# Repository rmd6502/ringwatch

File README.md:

## Welcome to GitHub Pages

You can use the [editor on GitHub](https://github.com/rmd6502/ringwatch/edit/master/README.md) to maintain and preview the content for your website in Markdown files.

Whenever you commit to this repository, GitHub Pages will run [Jekyll](https://jekyllrb.com/) to rebuild the pages in your site, from the content in your Markdown files.

### Markdown

Markdown is a lightweight and easy-to-use syntax for styling your writing. It includes conventions for

```markdown
Syntax highlighted code block

# Header 1
## Header 2
### Header 3

- Bulleted
- List

1. Numbered
2. List

**Bold** and _Italic_ and `Code` text

[Link](url) and 
```

For more details see [GitHub Flavored Markdown](https://guides.github.com/features/mastering-markdown/).

### Jekyll Themes

Your Pages site will use the layout and styles from the Jekyll theme you have selected in your [repository settings](https://github.com/rmd6502/ringwatch/settings). The name of this theme is saved in the Jekyll `_config.yml` configuration file.

### Support or Contact

Having trouble with Pages? Check out our [documentation](https://help.github.com/categories/github-pages-basics/) or [contact support](https://github.com/contact) and we’ll help you sort it out.

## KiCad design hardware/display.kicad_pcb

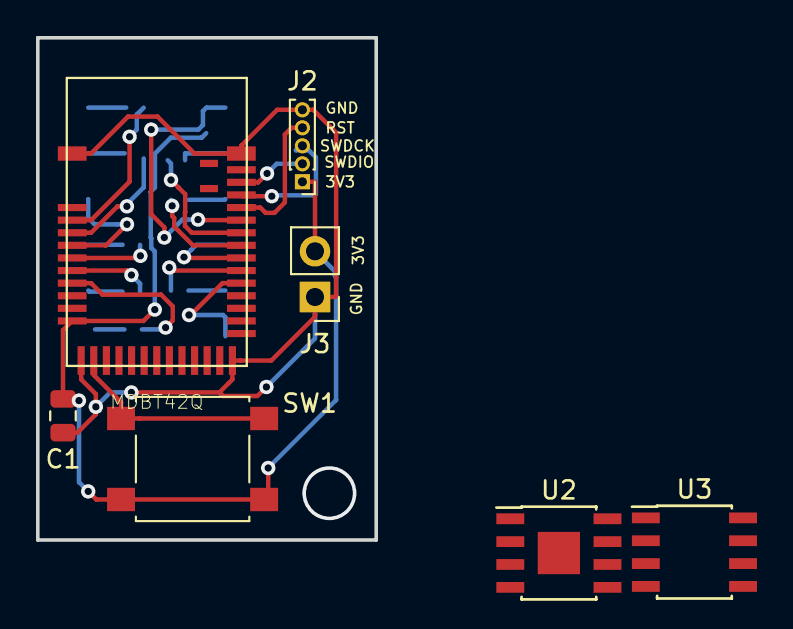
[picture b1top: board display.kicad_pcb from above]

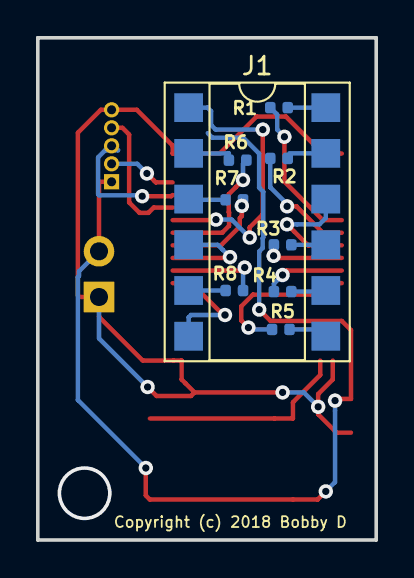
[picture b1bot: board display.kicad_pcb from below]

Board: 2 copper layers, 18.8 x 27.9 mm, 16 parts (9 on the bottom side), 28 nets.

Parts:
C1: .1µ; C_0805_2012Metric
J1: Conn_02x06_Counter_Clockwise; DIP-12_W7.62mm_SMDSocket_SmallPads
J2: Conn_01x05_Female; PinHeader_1x05_P1.00mm_Vertical
J3: Conn_01x02_Female; PinHeader_1x02_P2.54mm_Vertical
R1, R2, R3, R4, R5, R6, R7, R8: 220; R_0402_1005Metric
SW1: SW_Push; SW_SPST_B3S-1000
U1: MDBT42Q
U2: AS5601; SOIC-8-1EP_3.9x4.9mm_P1.27mm_EP2.35x2.35mm
U3: DS3231MZ; SOIC-8_3.9x4.9mm_P1.27mm

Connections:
+3V3: C1.1, J2.1, J3.2, SW1.2, U1.11
/A.: J1.5, R8.1
/Aa: J1.12, R1.2
/Ab: J1.11, R2.2
/Ac: J1.3, R7.1
/Ad: J1.8, R4.2
/Ae: J1.2, R6.1
/Af: J1.9, R3.2
/Ag: J1.7, R5.2
/K1: J1.1, U1.34
/K2: J1.10, U1.5
/K3: J1.4, U1.31
/K4: J1.6, U1.29
/SWDCK: J2.3, U1.36
/SWDIO: J2.2, U1.37
/i2c_subsystem/SCL: U1.25, U2.7, U3.8
/i2c_subsystem/SDA: U1.26, U2.6, U3.7
/tRST: J2.4, U1.35
GND: C1.2, J2.5, J3.1, U1.1, U1.12, U1.24, U1.39
unnamed: R1.1, U1.3
unnamed: R2.1, U1.4
unnamed: R3.1, U1.6
unnamed: R4.1, U1.7
unnamed: R5.1, U1.8
unnamed: R6.2, U1.33
unnamed: R7.2, U1.32
unnamed: R8.2, U1.30
unnamed: SW1.1, U1.13

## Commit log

2018-11-02 initial
2018-11-02 update labels
2018-11-02 label tweaks
2018-11-02 add pdfs
2018-11-02 update images
2018-11-03 update 3d
2018-11-03 more 3d
2018-11-07 organize a bit
2018-11-07 update watch
2018-11-08 update brightness
2018-11-08 Set theme jekyll-theme-minimal
2018-11-19 add setclock command line tool
2018-11-22 add i2c

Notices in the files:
hardware/display.kicad_pcb:
Copyright (c) 2018 Bobby D
